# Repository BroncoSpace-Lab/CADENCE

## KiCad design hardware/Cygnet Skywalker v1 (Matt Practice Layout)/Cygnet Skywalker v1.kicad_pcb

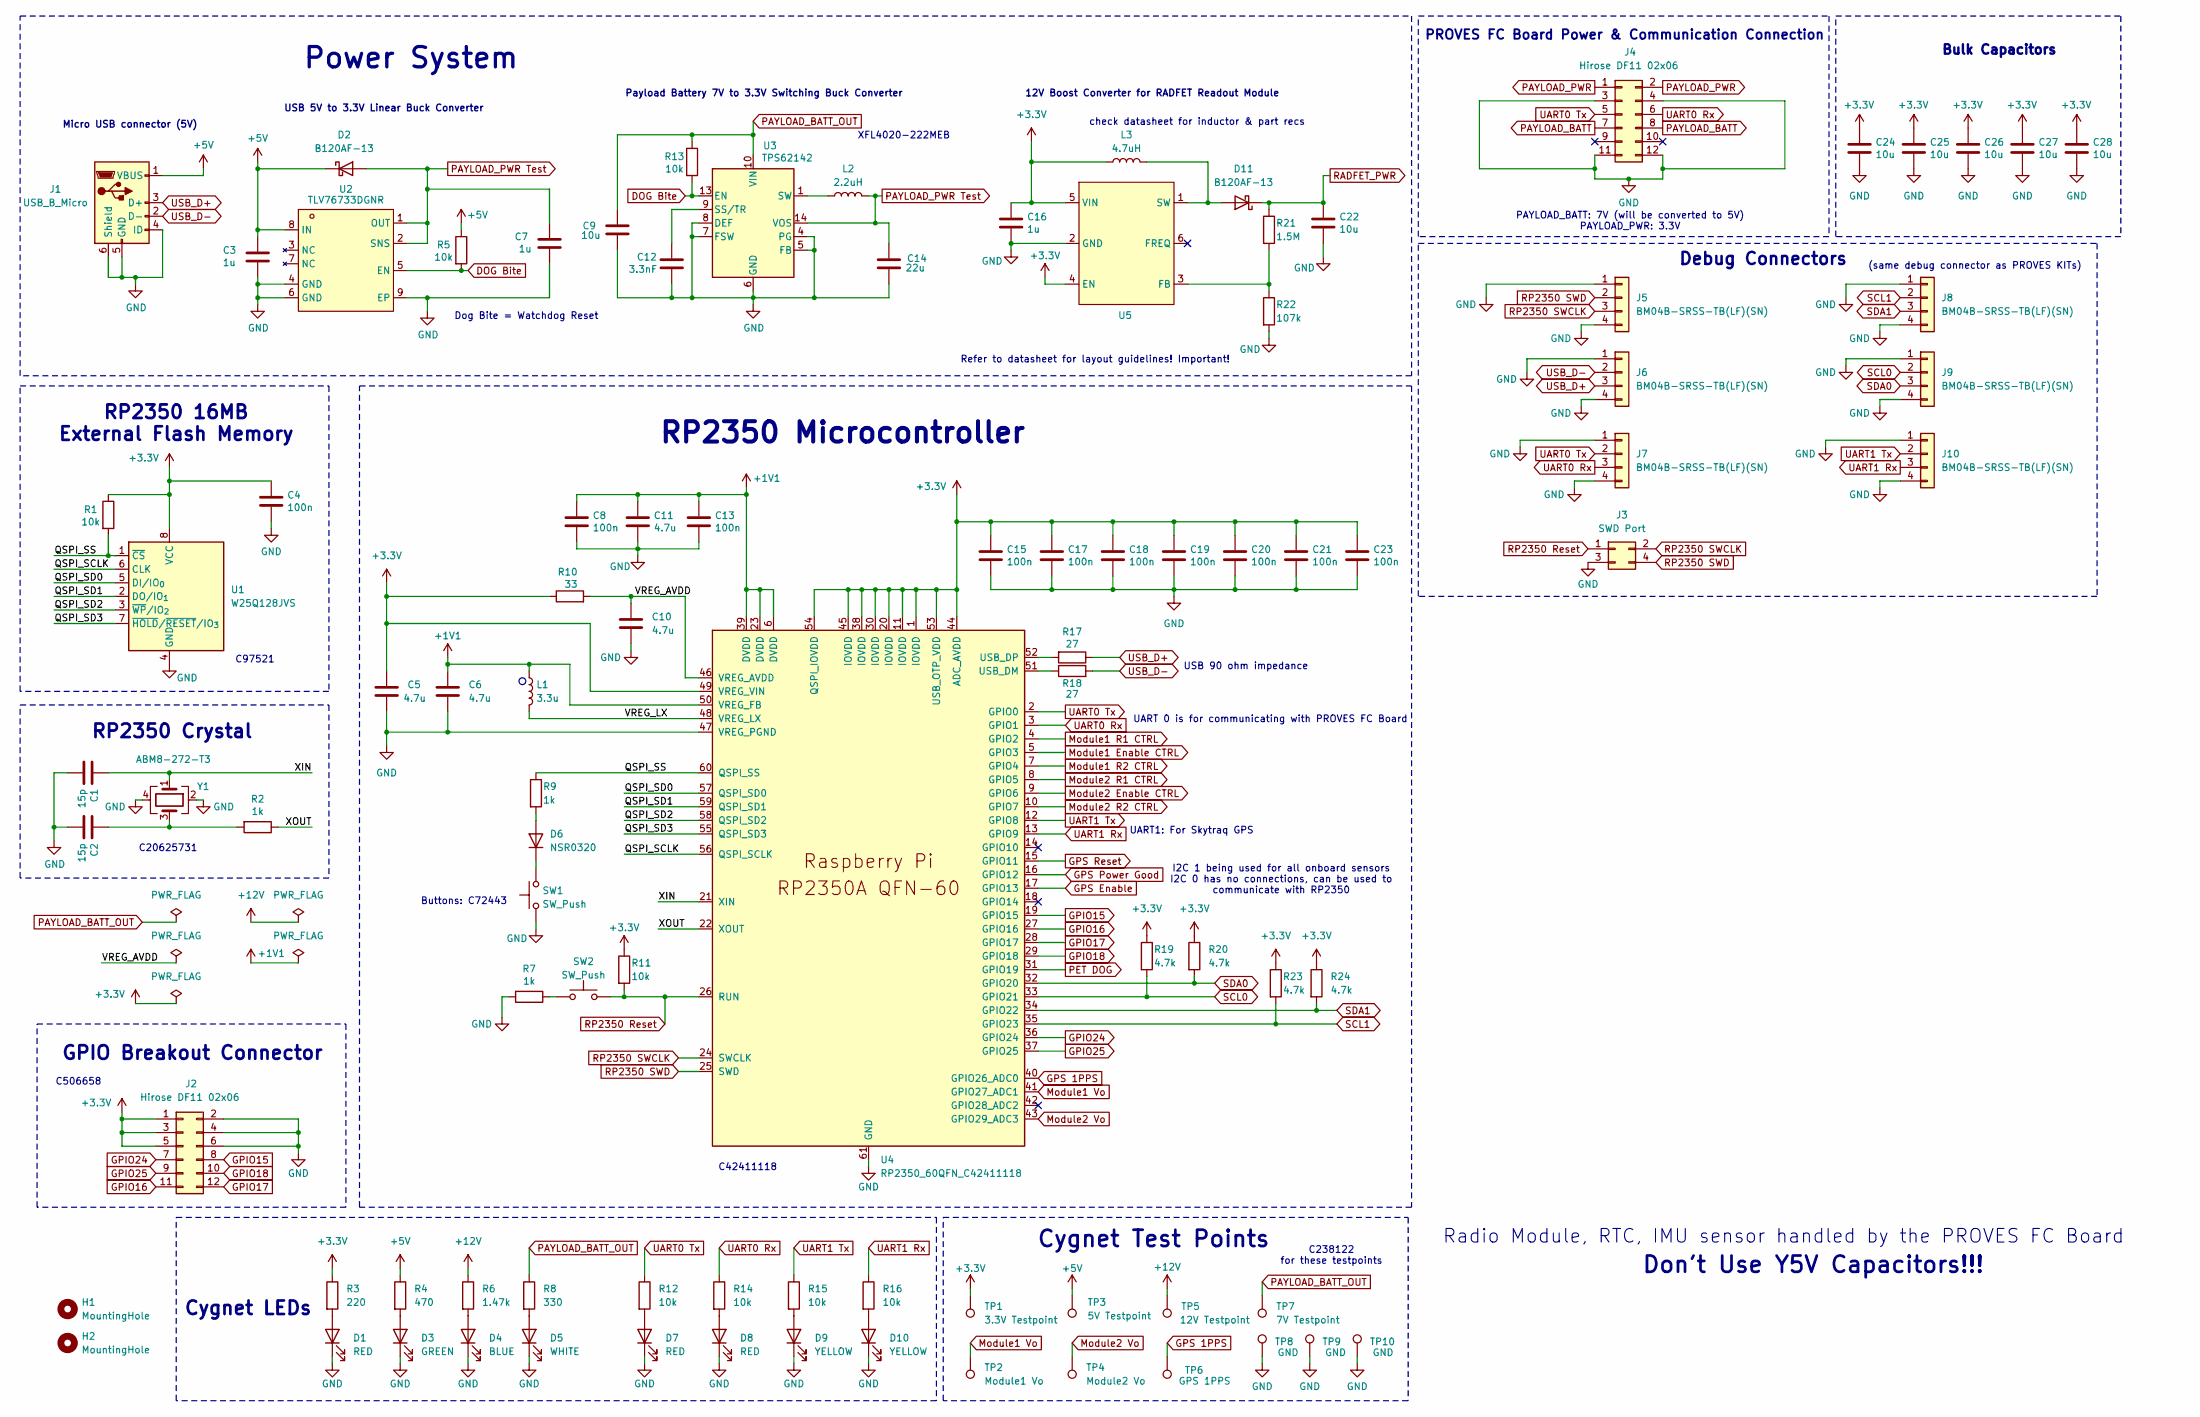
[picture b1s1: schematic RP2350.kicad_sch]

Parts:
C1, C2: 15p; C_0402_1005Metric
C3, C7, C16: 1u; C_0603_1608Metric
C4, C8, C13, C15, C17, C18, C19, C20, C21, C23: 100n; C_0402_1005Metric
C5, C6, C10, C11: 4.7u; C_0402_1005Metric
C9, C24, C25, C26, C27, C28: 10u; C_0805_2012Metric
C12: 3.3nF; C_0603_1608Metric
C14: 22u; C_1206_3216Metric
C22: 10u; C_1206_3216Metric
D1, D7, D8: RED; LED_0603_1608Metric
D2, D11: B120AF-13
D3: GREEN; LED_0603_1608Metric
D4: BLUE; LED_0603_1608Metric
D5: WHITE; LED_0603_1608Metric
D6: NSR0320; D_SOD-323F
D9, D10: YELLOW; LED_0603_1608Metric
H1, H2: MountingHole
J1: USB_B_Micro; MICRO-USB-SMD_10118194-0001LF
J2, J4: Hirose DF11 02x06; Hirose_DF11-12DP-2DSA_2x06_P2.00mm_Vertical
J3: SWD Port; PinHeader_2x02_P1.27mm_Vertical
J5, J6, J7, J8, J9, J10: BM04B-SRSS-TB(LF)(SN)
L1: 3.3u; L_pol_2016
L2: 2.2uH; L_Coilcraft_XxL4020
L3: 4.7uH; SWPA5040S4R7NT
R1, R5, R13: 10k; R_0402_1005Metric
R2, R7, R9: 1k; R_0402_1005Metric
R3: 220; R_0603_1608Metric
R4: 470; R_0603_1608Metric
R6: 1.47k; R_0603_1608Metric
R8: 330; R_0603_1608Metric
R10: 33; R_0402_1005Metric
R11: 10k; C_0402_1005Metric
R12, R14, R15, R16: 10k; R_0603_1608Metric
R17, R18: 27; R_0402_1005Metric
R19, R20, R23, R24: 4.7k; R_0402_1005Metric
R21: 1.5M; R_0603_1608Metric
R22: 107k; R_0603_1608Metric
SW1, SW2: SW_Push; KEY-SMD_KMR2XXGXXX
TP1: 3.3V Testpoint; Keystone5001_Testpoint
TP2: Module1 Vo; Keystone5001_Testpoint
TP3: 5V Testpoint; Keystone5001_Testpoint
TP4: Module2 Vo; Keystone5001_Testpoint
TP5: 12V Testpoint; Keystone5001_Testpoint
TP6: GPS 1PPS; Keystone5001_Testpoint
TP7: 7V Testpoint; Keystone5001_Testpoint
TP8, TP9, TP10: GND; Keystone5001_Testpoint
U1: W25Q128JVS; SOIC-8_5.3x5.3mm_P1.27mm
U2: TLV76733DGNR; LCSC Part C2873382
U3: TPS62142; VQFN-16-1EP_3x3mm_P0.5mm_EP1.68x1.68mm_ThermalVias
U4: RP2350_60QFN_C42411118; RP2350-QFN-60-1EP_7x7_P0.4mm_EP3.4x3.4mm_ThermalVias
U5: TLV61048; SOT-23-6
Y1: ABM8-272-T3

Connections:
+1V1: C6.1, C8.1, C11.1, C13.1, L1.1, U4.6 (DVDD), U4.23 (DVDD), U4.39 (DVDD), U4.50 (VREG_FB)
+3.3V: C4.1, C5.1, C15.1, C16.1, C17.1, C18.1, C19.1, C20.1, C21.1, C23.1, C24.1, C25.1, C26.1, C27.1, C28.1, J2.1, J2.3, J2.5, L3.1, R1.1, R3.1, R10.1, R11.1, R19.1, R20.1, R23.1, R24.1, TP1.1, U1.8 (VCC), U4.1 (IOVDD), U4.11 (IOVDD), U4.20 (IOVDD), U4.30 (IOVDD), U4.38 (IOVDD), U4.44 (ADC_AVDD), U4.45 (IOVDD), U4.49 (VREG_VIN), U4.53 (USB_OTP_VDD), U4.54 (QSPI_IOVDD), U5.4 (EN), U5.5 (VIN); also elsewhere on the board
+5V: C3.1, D2.1 (K), J1.1 (VBUS), R4.1, R5.1, TP3.1, U2.8 (IN)
+12V: R6.1, TP5.1; also elsewhere on the board
/RP2350/QSPI_SCLK: U1.6 (CLK), U4.56 (QSPI_SCLK)
/RP2350/QSPI_SD0: U1.5 (DI/IO_{0}), U4.57 (QSPI_SD0)
/RP2350/QSPI_SD1: U1.2 (DO/IO_{1}), U4.59 (QSPI_SD1)
/RP2350/QSPI_SD2: U1.3 (~WP/IO_{2}), U4.58 (QSPI_SD2)
/RP2350/QSPI_SD3: U1.7 (~HOLD/~RESET/IO_{3}), U4.55 (QSPI_SD3)
/RP2350/QSPI_SS: R1.2, R9.1, U1.1 (~CS), U4.60 (QSPI_SS)
/RP2350/VREG_AVDD: C10.1, R10.2, U4.46 (VREG_AVDD)
/RP2350/VREG_LX: L1.2, U4.48 (VREG_LX)
/RP2350/XIN: C1.1, U4.21 (XIN), Y1.1
/RP2350/XOUT: R2.1, U4.22 (XOUT)
DOG Bite: R5.2, R13.2, U2.5 (EN), U3.13 (EN); also elsewhere on the board
GND: C1.2, C2.2, C3.2, C4.2, C5.2, C6.2, C7.2, C8.2, C9.2, C10.2, C11.2, C12.2, C13.2, C14.2, C15.2, C16.2, C17.2, C18.2, C19.2, C20.2, C21.2, C22.2, C23.2, C24.2, C25.2, C26.2, C27.2, C28.2, D1.1 (K), D3.1 (K), D4.1 (K), D5.1 (K), D7.1 (K), D8.1 (K), D9.1 (K), D10.1 (K), J1.4 (ID), J1.5 (GND), J1.6 (Shield), J2.2, J2.4, J2.6, J3.3, J4.3, J4.4, J4.11, J4.12, J5.1, J5.4, J6.1, J6.4, J7.1, J7.4, J8.1, J8.4, J9.1, J9.4, J10.1, J10.4, R7.2, R22.2, SW1.1, TP8.1, TP9.1, TP10.1, U1.4 (GND), U2.4 (GND), U2.6 (GND), U2.9 (EP), U3.4 (PG), U3.5 (FB), U3.6 (GND), U3.7 (FSW), U3.8 (DEF), U3.15 (GND), U3.16 (GND), U3.17 (GND), U4.47 (VREG_PGND), U4.61 (GND), U5.2 (GND), Y1.2, Y1.4; also elsewhere on the board
GPIO15: J2.8, U4.19 (GPIO15)
GPIO16: J2.11, U4.27 (GPIO16)
GPIO17: J2.12, U4.28 (GPIO17)
GPIO18: J2.10, U4.29 (GPIO18)
GPIO24: J2.7, U4.36 (GPIO24)
GPIO25: J2.9, U4.37 (GPIO25)
GPS 1PPS: TP6.1, U4.40 (GPIO26_ADC0); also elsewhere on the board
GPS Enable: U4.17 (GPIO13); also elsewhere on the board
GPS Power Good: U4.16 (GPIO12); also elsewhere on the board
GPS Reset: U4.15 (GPIO11); also elsewhere on the board
Module1 Enable CTRL: U4.5 (GPIO3); also elsewhere on the board
Module1 R1 CTRL: U4.4 (GPIO2); also elsewhere on the board
Module1 R2 CTRL: U4.7 (GPIO4); also elsewhere on the board
Module1 Vo: TP2.1, U4.41 (GPIO27_ADC1); also elsewhere on the board
Module2 Enable CTRL: U4.9 (GPIO6); also elsewhere on the board
Module2 R1 CTRL: U4.8 (GPIO5); also elsewhere on the board
Module2 R2 CTRL: U4.10 (GPIO7); also elsewhere on the board
Module2 Vo: TP4.1, U4.43 (GPIO29_ADC3); also elsewhere on the board
unnamed: C2.1, R2.2, Y1.3
unnamed: D1.2 (A), R3.2
unnamed: D3.2 (A), R4.2
unnamed: D4.2 (A), R6.2
unnamed: D5.2 (A), R8.2
unnamed: D6.2 (A), R9.2
unnamed: D6.1 (K), SW1.3 (2)
unnamed: D7.2 (A), R12.2
unnamed: D8.2 (A), R14.2
unnamed: D9.2 (A), R15.2
unnamed: D10.2 (A), R16.2
unnamed: D11.2 (A), L3.2, U5.1 (SW)
unnamed: L2.1, U3.1 (SW), U3.2 (SW), U3.3 (SW)
unnamed: R7.1, SW2.1
unnamed: C12.1, U3.9 (SS/TR)
unnamed: R18.1, U4.51 (USB_DM)
unnamed: R17.2, U4.52 (USB_DP)
unnamed: R21.2, R22.1, U5.3 (FB)
PAYLOAD_BATT: J4.7, J4.8; also elsewhere on the board
PAYLOAD_BATT_OUT: C9.1, R8.1, R13.1, TP7.1, U3.10 (VIN), U3.11 (VIN), U3.12 (VIN); also elsewhere on the board
PAYLOAD_PWR: J4.1, J4.2
PAYLOAD_PWR Test: C7.1, C14.1, D2.2 (A), L2.2, U2.1 (OUT), U2.2 (SNS), U3.14 (VOS); also elsewhere on the board
PET DOG: U4.31 (GPIO19); also elsewhere on the board
RADFET_PWR: C22.1, D11.1 (K), R21.1; also elsewhere on the board
RP2350 Reset: J3.1, R11.2, SW2.3 (2), U4.26 (RUN)
RP2350 SWCLK: J3.2, J5.3, U4.24 (SWCLK)
RP2350 SWD: J3.4, J5.2, U4.25 (SWD)
SCL0: J9.2, R19.2, U4.33 (GPIO21)
SCL1: J8.2, R23.2, U4.35 (GPIO23); also elsewhere on the board
SDA0: J9.3, R20.2, U4.32 (GPIO20)
SDA1: J8.3, R24.2, U4.34 (GPIO22); also elsewhere on the board
UART0 Rx: J4.6, J7.3, R14.1, U4.3 (GPIO1)
UART0 Tx: J4.5, J7.2, R12.1, U4.2 (GPIO0)
UART1 Rx: J10.3, R16.1, U4.13 (GPIO9); also elsewhere on the board
UART1 Tx: J10.2, R15.1, U4.12 (GPIO8); also elsewhere on the board
USB_D+: J1.3 (D+), J6.3, R17.1
USB_D-: J1.2 (D-), J6.2, R18.2

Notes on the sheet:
GPIO Breakout Connector
PROVES FC Board Power & Communication Connection
XFL4020-222MEB
12V Boost Converter for RADFET Readout Module
Cygnet Test Points
UART 0 is for communicating with PROVES FC Board
USB 90 ohm impedance
Payload Battery 7V to 3.3V Switching Buck Converter
C506658
Buttons: C72443
C42411118
C20625731
USB 5V to 3.3V Linear Buck Converter
UART1: For Skytraq GPS
RP2350 Microcontroller
I2C 1 being used for all onboard sensors I2C 0 has no connections, can be used to communicate with RP2350
Dog Bite = Watchdog Reset
Bulk Capacitors
check datasheet for inductor & part recs
PAYLOAD_BATT: 7V (will be converted to 5V) PAYLOAD_PWR: 3.3V
Don't Use Y5V Capacitors!!!
C97521
Micro USB connector (5V)
C238122 for these testpoints
Power System
(same debug connector as PROVES KITs)
Radio Module, RTC, IMU sensor handled by the PROVES FC Board
RP2350 Crystal
Debug Connectors
Refer to datasheet for layout guidelines! Important!
RP2350 16MB External Flash Memory
Cygnet LEDs

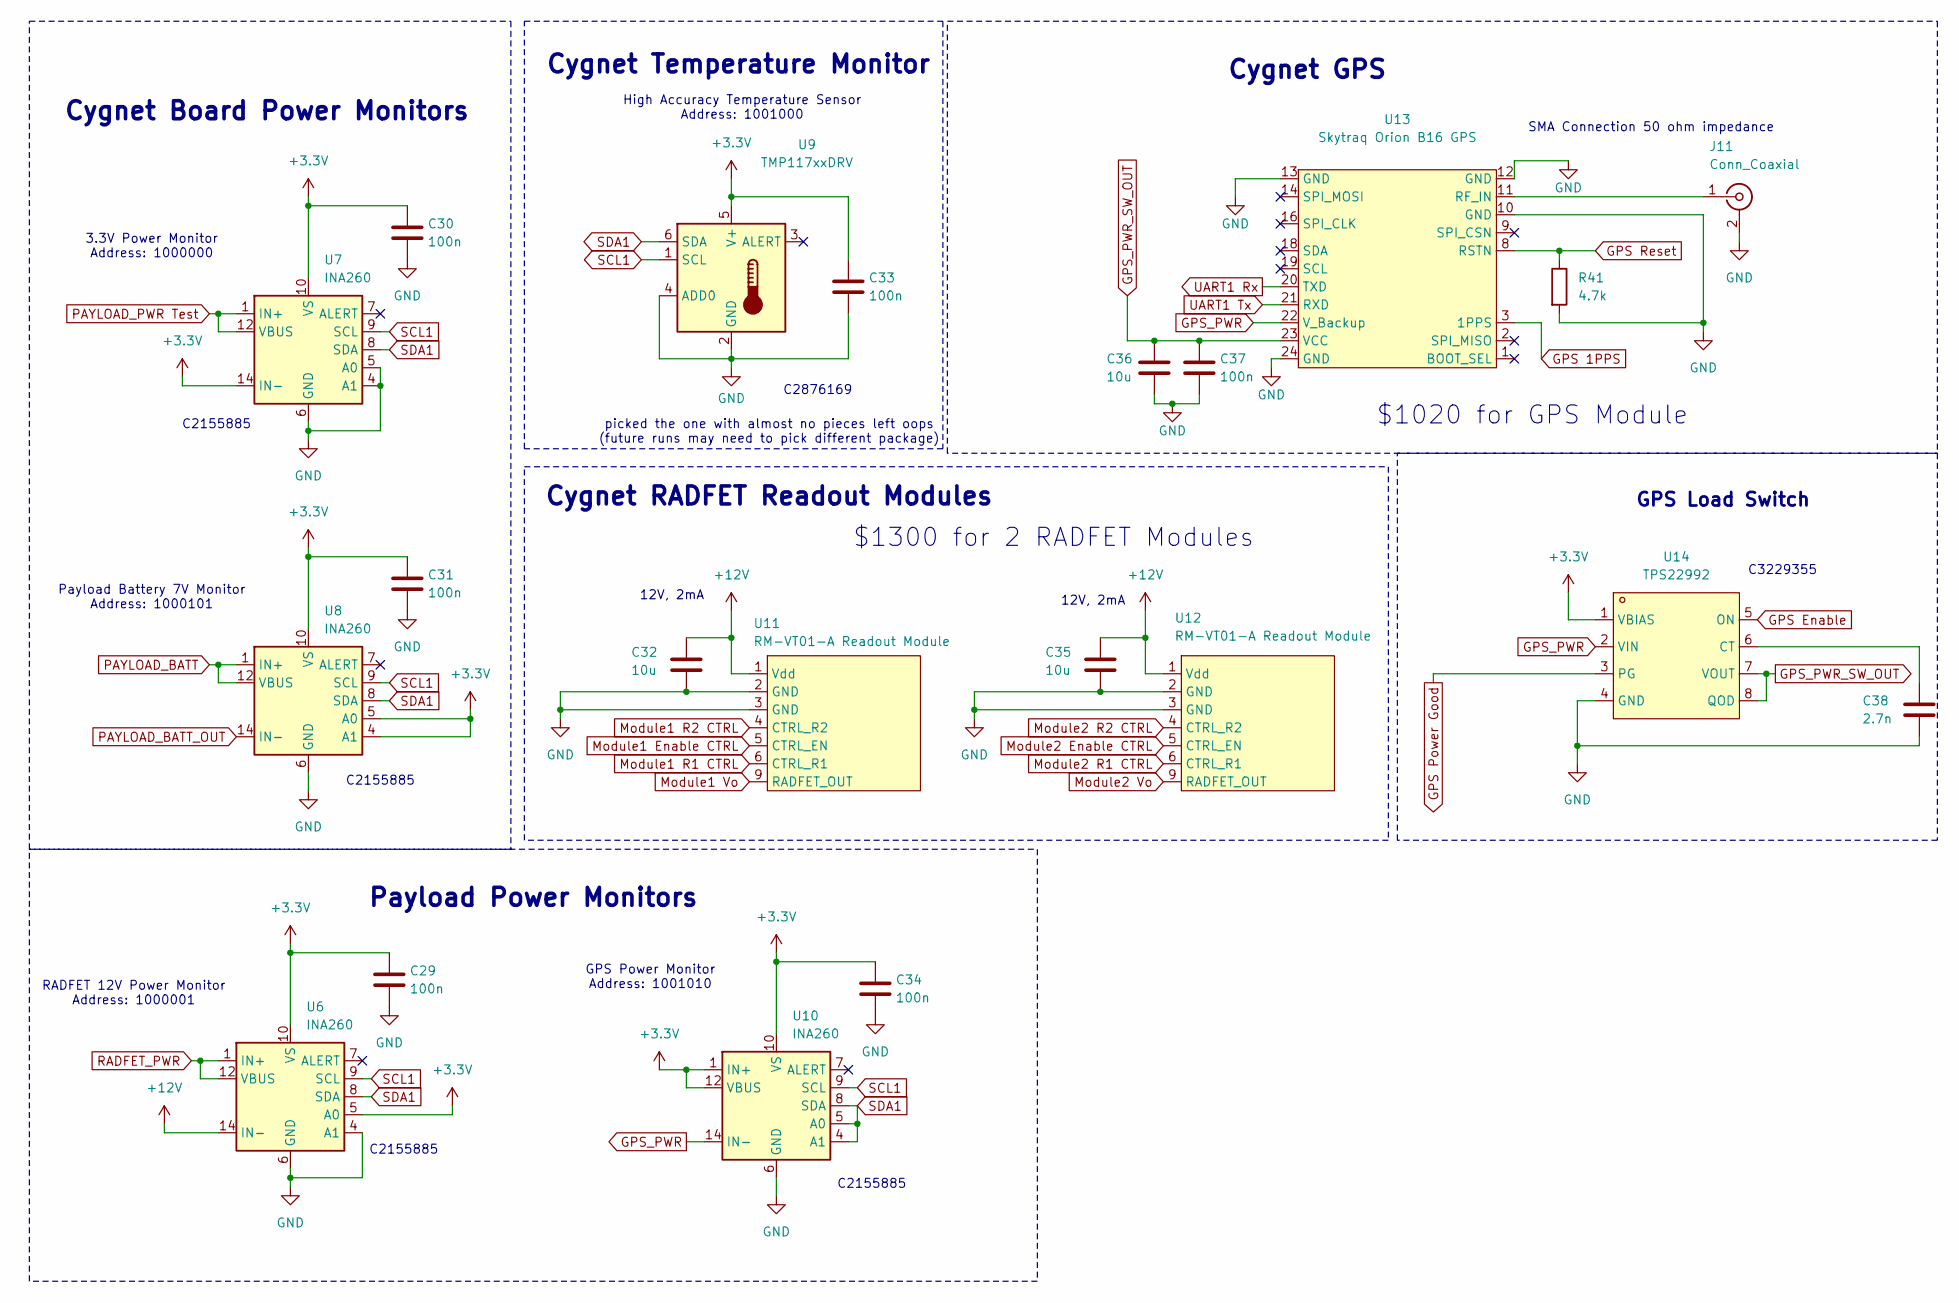
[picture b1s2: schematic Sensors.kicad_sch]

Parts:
C29, C30, C31, C33, C34, C37: 100n; C_0402_1005Metric
C32, C35: 10u; C_1206_3216Metric
C36: 10u; C_0805_2012Metric
C38: 2.7n; C_0603_1608Metric
J11: Conn_Coaxial; SMA-TH_132134
R41: 4.7k; R_0402_1005Metric
U6, U7, U8, U10: INA260; TSSOP-16_4.4x5mm_P0.65mm
U9: TMP117xxDRV; WSON-6-1EP_2x2mm_P0.65mm_EP1x1.6mm
U11, U12: RM-VT01-A Readout Module; RM-VT01-A
U13: Skytraq Orion B16 GPS
U14: TPS22992

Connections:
+3.3V: C29.1, C30.1, C31.1, C33.1, C34.1, U6.5 (A0), U6.10 (VS), U7.10 (VS), U7.14 (IN-), U7.15 (IN-), U7.16 (IN-), U8.4 (A1), U8.5 (A0), U8.10 (VS), U9.5 (V+), U10.1 (IN+), U10.2 (IN+), U10.3 (IN+), U10.10 (VS), U10.12 (VBUS), U14.1 (VBIAS); also elsewhere on the board
+12V: C32.1, C35.1, U6.14 (IN-), U6.15 (IN-), U6.16 (IN-), U11.1 (Vdd), U12.1 (Vdd); also elsewhere on the board
GND: C29.2, C30.2, C31.2, C32.2, C33.2, C34.2, C35.2, C36.2, C37.2, C38.2, J11.2 (Ext), R41.2, U6.4 (A1), U6.6 (GND), U6.11 (GND), U7.4 (A1), U7.5 (A0), U7.6 (GND), U7.11 (GND), U8.6 (GND), U8.11 (GND), U9.2 (GND), U9.4 (ADD0), U10.6 (GND), U10.11 (GND), U11.2 (GND), U11.3 (GND), U12.2 (GND), U12.3 (GND), U13.10 (GND), U13.12 (GND), U13.13 (GND), U13.24 (GND), U14.4 (GND); also elsewhere on the board
GPS 1PPS: U13.3 (1PPS); also elsewhere on the board
GPS Enable: U14.5 (ON); also elsewhere on the board
GPS Power Good: U14.3 (PG); also elsewhere on the board
GPS Reset: R41.1, U13.8 (RSTN); also elsewhere on the board
GPS_PWR: U10.14 (IN-), U10.15 (IN-), U10.16 (IN-), U13.22 (V_Backup), U14.2 (VIN)
GPS_PWR_SW_OUT: C36.1, C37.1, U13.23 (VCC), U14.7 (VOUT), U14.8 (QOD)
Module1 Enable CTRL: U11.5 (CTRL_EN); also elsewhere on the board
Module1 R1 CTRL: U11.6 (CTRL_R1); also elsewhere on the board
Module1 R2 CTRL: U11.4 (CTRL_R2); also elsewhere on the board
Module1 Vo: U11.9 (RADFET_OUT); also elsewhere on the board
Module2 Enable CTRL: U12.5 (CTRL_EN); also elsewhere on the board
Module2 R1 CTRL: U12.6 (CTRL_R1); also elsewhere on the board
Module2 R2 CTRL: U12.4 (CTRL_R2); also elsewhere on the board
Module2 Vo: U12.9 (RADFET_OUT); also elsewhere on the board
unnamed: J11.1 (In), U13.11 (RF_IN)
unnamed: C38.1, U14.6 (CT)
PAYLOAD_BATT: U8.1 (IN+), U8.2 (IN+), U8.3 (IN+), U8.12 (VBUS); also elsewhere on the board
PAYLOAD_BATT_OUT: U8.14 (IN-), U8.15 (IN-), U8.16 (IN-); also elsewhere on the board
PAYLOAD_PWR Test: U7.1 (IN+), U7.2 (IN+), U7.3 (IN+), U7.12 (VBUS); also elsewhere on the board
RADFET_PWR: U6.1 (IN+), U6.2 (IN+), U6.3 (IN+), U6.12 (VBUS); also elsewhere on the board
SCL1: U6.9 (SCL), U7.9 (SCL), U8.9 (SCL), U9.1 (SCL), U10.9 (SCL); also elsewhere on the board
SDA1: U6.8 (SDA), U7.8 (SDA), U8.8 (SDA), U9.6 (SDA), U10.4 (A1), U10.5 (A0), U10.8 (SDA); also elsewhere on the board
UART1 Rx: U13.20 (TXD); also elsewhere on the board
UART1 Tx: U13.21 (RXD); also elsewhere on the board

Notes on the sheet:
C2155885
Cygnet GPS
C3229355
Payload Power Monitors
$1300 for 2 RADFET Modules
GPS Power Monitor Address: 1001010
$1020 for GPS Module
picked the one with almost no pieces left oops (future runs may need to pick different package)
SMA Connection 50 ohm impedance
12V, 2mA
Payload Battery 7V Monitor Address: 1000101
Cygnet RADFET Readout Modules
RADFET 12V Power Monitor Address: 1000001
GPS Load Switch
Cygnet Temperature Monitor
Cygnet Board Power Monitors
C2876169
High Accuracy Temperature Sensor Address: 1001000
3.3V Power Monitor Address: 1000000

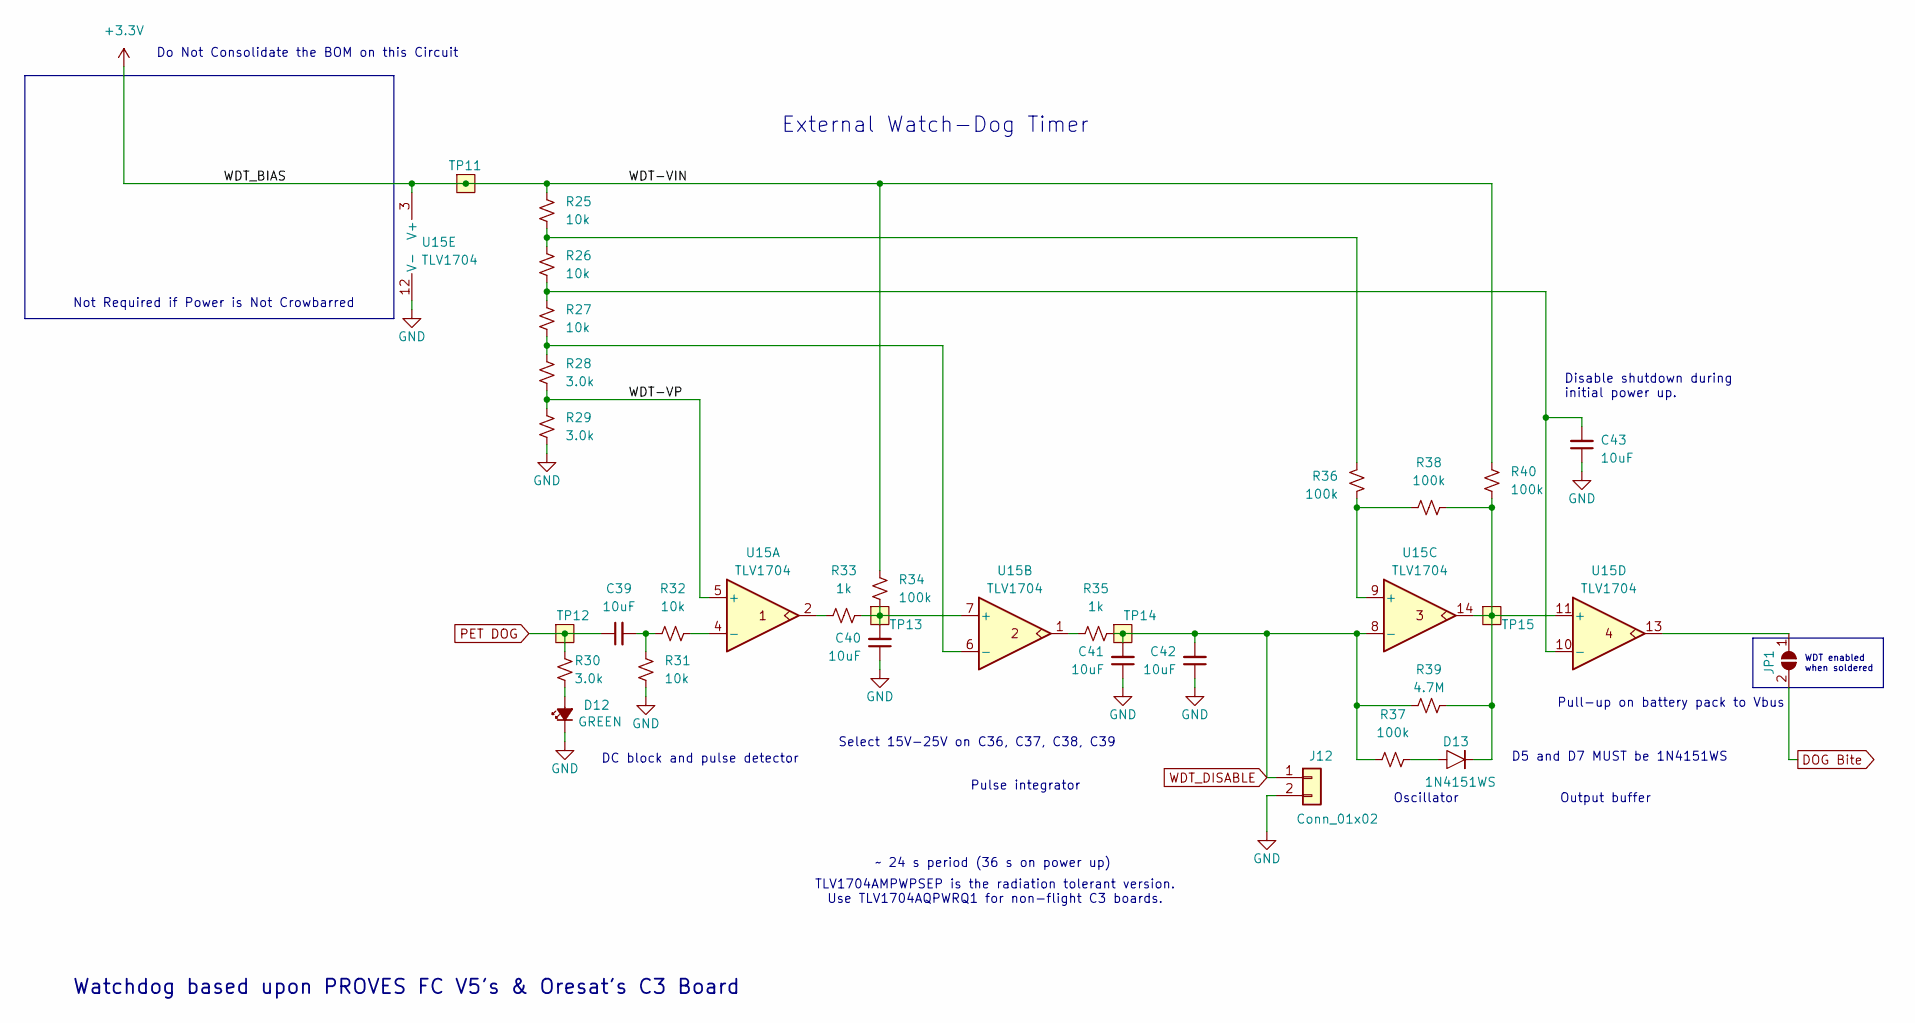
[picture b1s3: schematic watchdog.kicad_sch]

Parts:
C39, C40, C41, C42, C43: 10uF; C_0603_1608Metric; MPN GRT188R61C106KE13D
D12: GREEN; LED_0603_1608Metric; MPN 150060GS75000
D13: 1N4151WS; D_SOD-323; MPN 1N4151WS-E3-08
J12: Conn_01x02; PinHeader_1x02_P2.54mm_Vertical
JP1: SolderJumper_2_Open; SolderJumper-2_P1.3mm_Open_RoundedPad1.0x1.5mm
R25, R26, R27, R31, R32: 10k; R_0603_1608Metric; MPN RMCF0603FT10K0
R28, R29, R30: 3.0k; R_0603_1608Metric; MPN RMCF0603FT3K00
R33, R35: 1k; R_0603_1608Metric; MPN RMCF0603FT1K00
R34, R36, R37, R38, R40: 100k; R_0603_1608Metric; MPN RMCF0603FT100K
R39: 4.7M; R_0603_1608Metric; MPN RMCF0603FT4M70
TP11, TP12, TP13, TP14, TP15: TestPoint-MinTH; TestPoint-0.75mm-th
U15: TLV1704; TSSOP-14_4.4x5mm_P0.65mm; MPN TLV1704AQPWRQ1

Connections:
+3.3V: R25.1, R34.1, R40.2, TP11.1, U15.3 (V+); also elsewhere on the board
/CubeSat's Best Friend/WDT-VP: R28.2, R29.1, U15.5 (+)
DOG Bite: JP1.2 (B); also elsewhere on the board
GND: C40.1, C41.1, C42.1, C43.1, D12.1 (K), J12.2, R29.2, R31.2, U15.12 (V-); also elsewhere on the board
unnamed: C39.2, R31.1, R32.1
unnamed: D12.2 (A), R30.2
unnamed: D13.2, R37.1
unnamed: JP1.1 (A), U15.13
unnamed: R25.2, R26.1, R36.2
unnamed: R33.1, U15.2
unnamed: R35.1, U15.1
unnamed: R32.2, U15.4 (-)
unnamed: C40.2, R33.2, R34.2, TP13.1, U15.7 (+)
unnamed: R27.2, R28.1, U15.6 (-)
unnamed: R36.1, R38.1, U15.9 (+)
unnamed: D13.1, R38.2, R39.1, R40.1, TP15.1, U15.11 (+), U15.14
unnamed: C43.2, R26.2, R27.1, U15.10 (-)
PET DOG: C39.1, R30.1, TP12.1; also elsewhere on the board
WDT_DISABLE: C41.2, C42.2, J12.1, R35.2, R37.2, R39.2, TP14.1, U15.8 (-)

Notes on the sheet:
Select 15V-25V on C36, C37, C38, C39
Watchdog based upon PROVES FC V5's & Oresat's C3 Board
Do Not Consolidate the BOM on this Circuit
D5 and D7 MUST be 1N4151WS
Disable shutdown during initial power up.
Oscillator
Pull-up on battery pack to Vbus
External Watch-Dog Timer
TLV1704AMPWPSEP is the radiation tolerant version. Use TLV1704AQPWRQ1 for non-flight C3 boards.
Pulse integrator
Not Required if Power is Not Crowbarred
DC block and pulse detector
Output buffer
WDT enabled when soldered
~ 24 s period (36 s on power up)

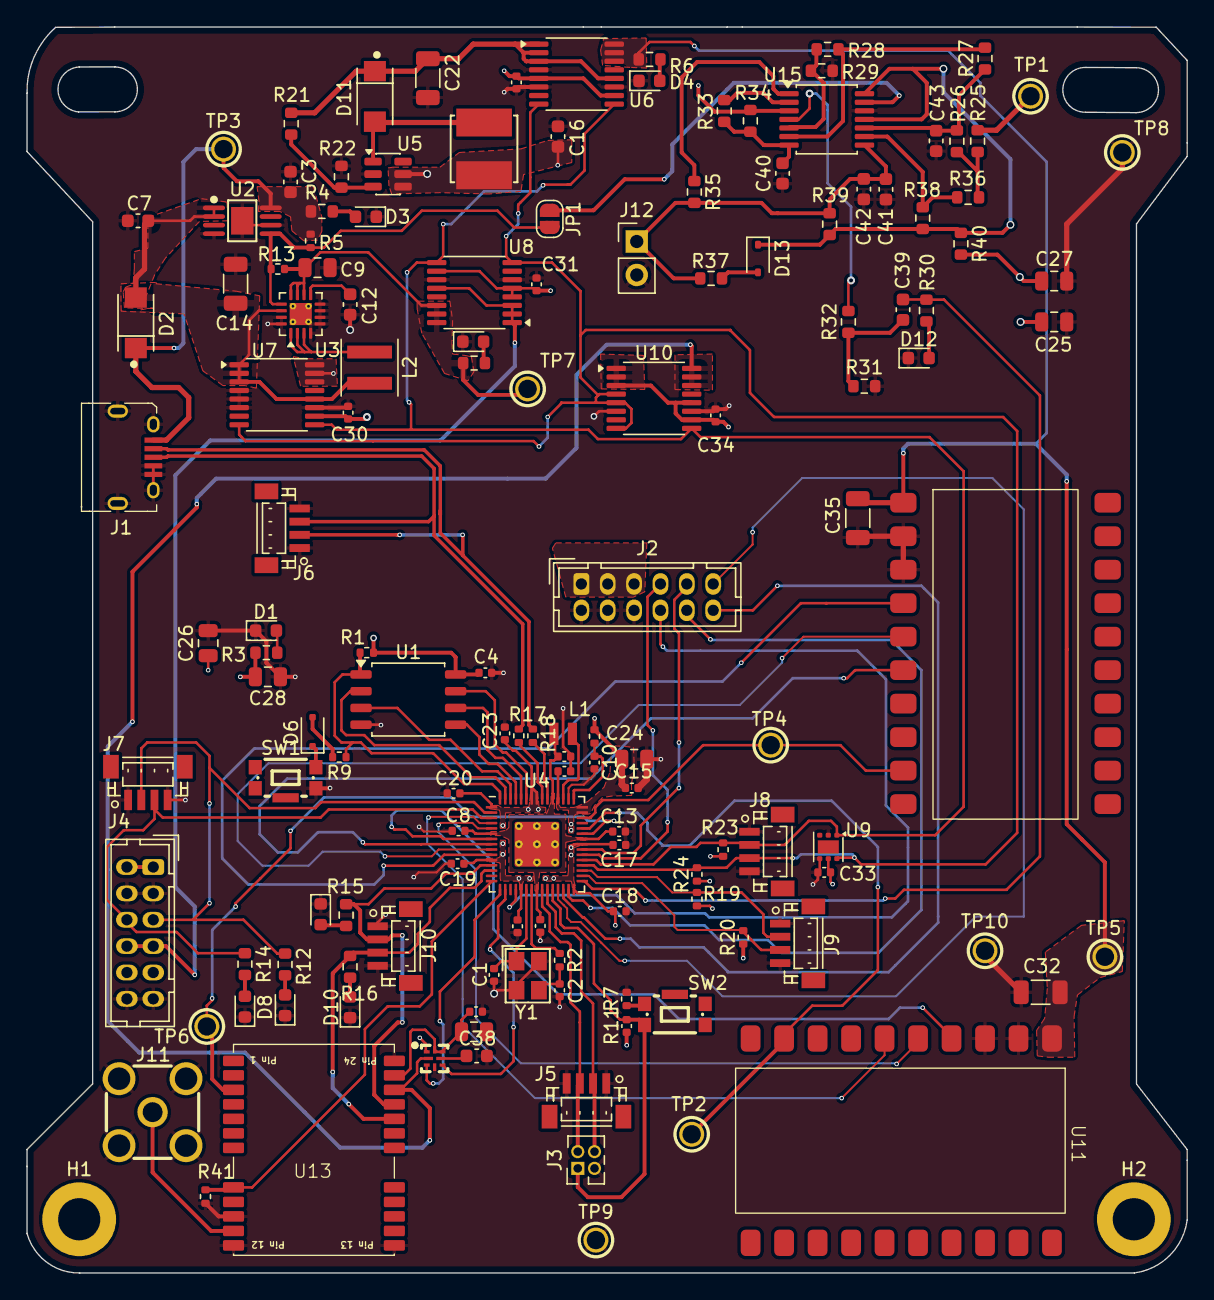
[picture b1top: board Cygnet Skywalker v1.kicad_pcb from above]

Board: 4 copper layers, 88.0 x 94.5 mm, 143 parts (0 on the bottom side), 90 nets.

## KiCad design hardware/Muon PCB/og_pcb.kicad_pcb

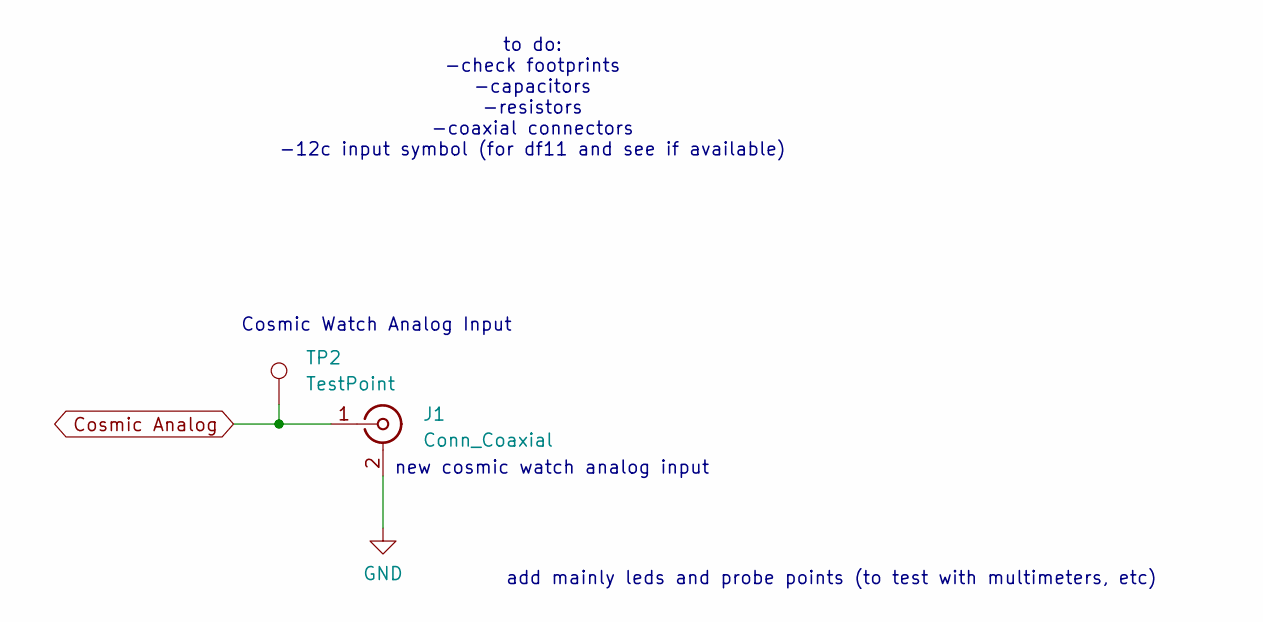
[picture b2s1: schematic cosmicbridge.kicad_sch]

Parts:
J1: Conn_Coaxial; MMCX_Molex_73415-1471_Vertical
TP2: TestPoint; TestPoint_Loop_D1.80mm_Drill1.0mm_Beaded

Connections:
Cosmic Analog: J1.1 (In), TP2.1; also elsewhere on the board
GND: J1.2 (Ext); also elsewhere on the board

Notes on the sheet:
add mainly leds and probe points (to test with multimeters, etc)
Cosmic Watch Analog Input
to do: -check footprints -capacitors -resistors -coaxial connectors -12c input symbol (for df11 and see if available)
new cosmic watch analog input

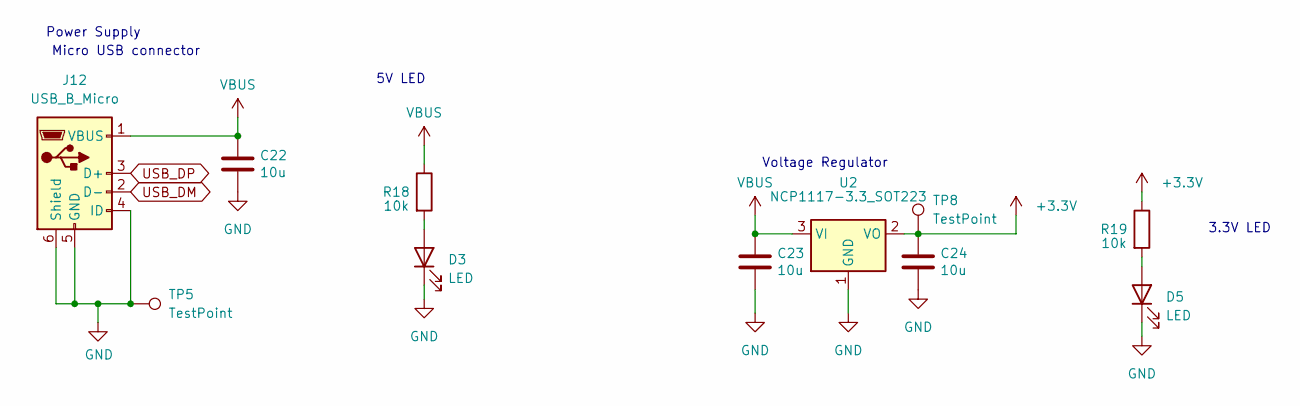
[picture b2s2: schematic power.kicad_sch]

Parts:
C22, C23, C24: 10u; C_0805_2012Metric
D3, D5: LED; LED_0402_1005Metric
J12: USB_B_Micro; microUSB
R18, R19: 10k; R_0402_1005Metric
TP5, TP8: TestPoint; TestPoint_Loop_D1.80mm_Drill1.0mm_Beaded
U2: NCP1117-3.3_SOT223; SOT-223-3_TabPin2

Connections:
+3.3V: C24.1, R19.1, TP8.1, U2.2 (VO); also elsewhere on the board
GND: C22.2, C23.2, C24.2, D3.1 (K), D5.1 (K), J12.4 (ID), J12.5 (GND), J12.6 (Shield), TP5.1, U2.1 (GND); also elsewhere on the board
unnamed: D3.2 (A), R18.2
unnamed: D5.2 (A), R19.2
USB_DM: J12.2 (D-); also elsewhere on the board
USB_DP: J12.3 (D+); also elsewhere on the board
VBUS: C22.1, C23.1, J12.1 (VBUS), R18.1, U2.3 (VI); also elsewhere on the board

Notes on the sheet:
3.3V LED
5V LED
Micro USB connector
Power Supply
Voltage Regulator
